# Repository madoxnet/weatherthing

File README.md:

# Weather Thing

## Test Version
One ESP8266
Two BME280
One I2C 0.96" OLED Display

## Libraries
<https://github.com/finitespace/BME280>
<https://github.com/squix78/esp8266-oled-ssd1306/>
<https://github.com/mathworks/thingspeak-arduino>

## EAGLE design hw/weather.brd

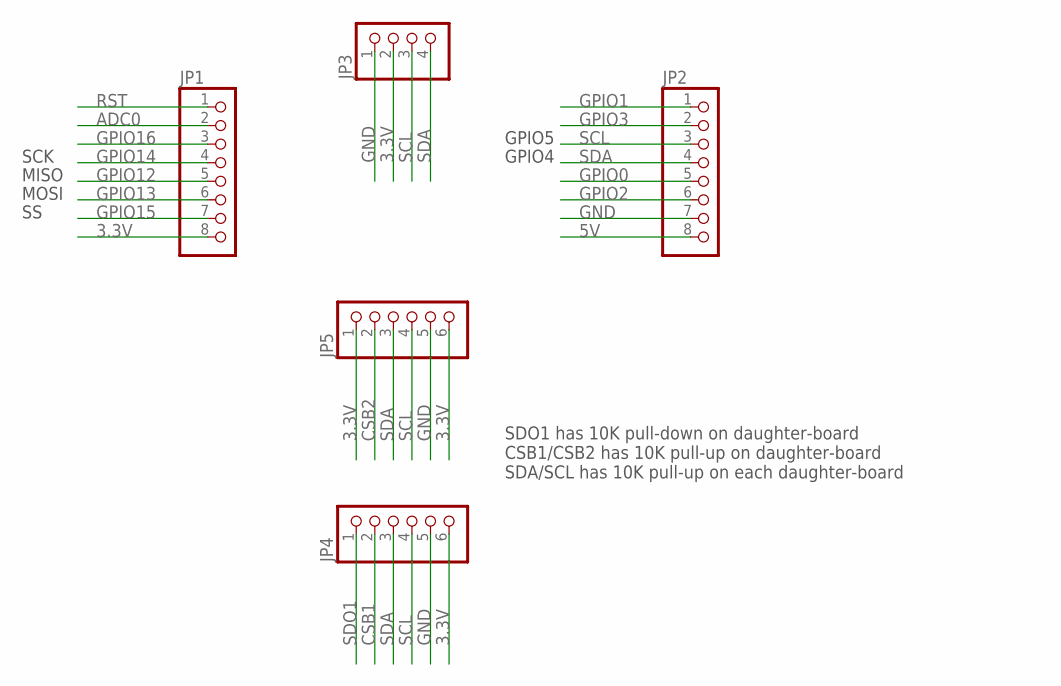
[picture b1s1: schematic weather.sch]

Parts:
JP1, JP2: PINHD-1X8; 1X08
JP3: PINHD-1X4; 1X04
JP4, JP5: PINHD-1X6; 1X06

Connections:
3.3V: JP1.8, JP3.2, JP4.6, JP5.1, JP5.6
5V: JP2.8
ADC0: JP1.2
CSB1: JP4.2
CSB2: JP5.2
GND: JP2.7, JP3.1, JP4.5, JP5.5
GPIO0: JP2.5
GPIO1: JP2.1
GPIO2: JP2.6
GPIO3: JP2.2
GPIO12: JP1.5
GPIO13: JP1.6
GPIO14: JP1.4
GPIO15: JP1.7
GPIO16: JP1.3
RST: JP1.1
SCL: JP2.3, JP3.3, JP4.4, JP5.4
SDA: JP2.4, JP3.4, JP4.3, JP5.3
SDO1: JP4.1

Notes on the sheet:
SCK
MISO
MOSI
GPIO4
GPIO5
SDO1 has 10K pull-down on daughter-board CSB1/CSB2 has 10K pull-up on daughter-board SDA/SCL has 10K pull-up on each daughter-board

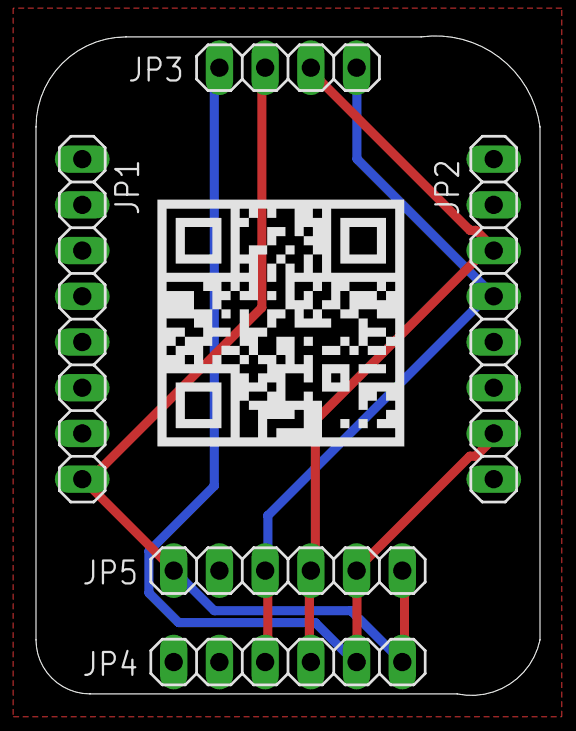
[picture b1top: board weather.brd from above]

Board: 2 copper layers, 28.0 x 36.6 mm, 7 parts (1 on the bottom side), 4 nets.

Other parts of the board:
U$1, U$2: MADOX

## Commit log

2017-07-09 :lollipop: Added .gitattributes & .gitignore files
2017-07-09 Iniital Commit
    Initial test board and schematics with functioning sensor read and
    display code.
2017-07-23 Add Thingspeak post
    Note various text cleanups still need to be done
